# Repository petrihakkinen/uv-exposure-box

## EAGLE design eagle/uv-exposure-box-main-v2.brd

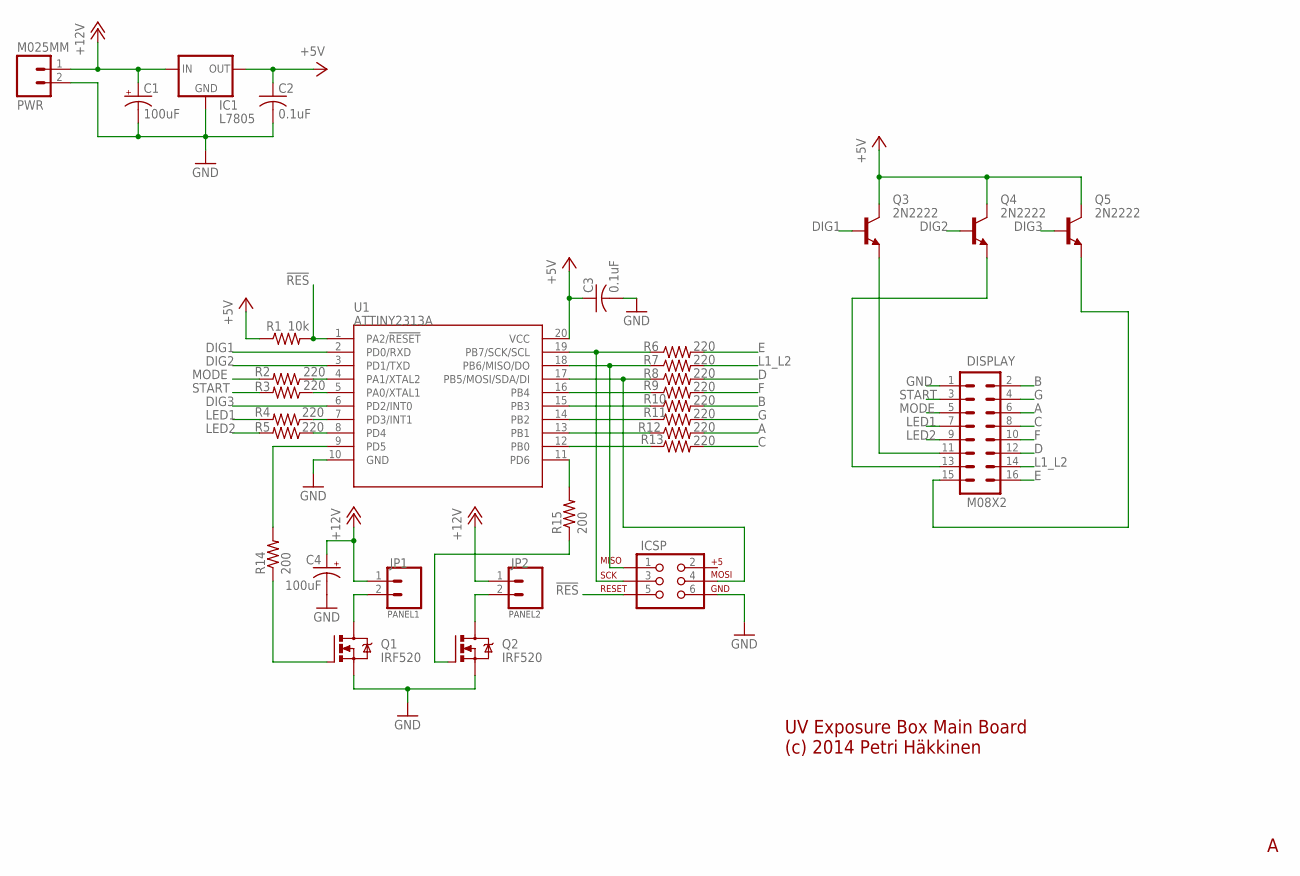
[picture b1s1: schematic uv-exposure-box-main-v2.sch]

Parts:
C1, C4: 100uF; E2,5-5
C2, C3: 0.1uF; C025-024X044
DISPLAY: M08X2; 2X8
IC1: L7805; TO220-IGO
ICSP: AVR_SPI_PRG_6PTH; 2X3
JP1, JP2: M025MM; SCREWTERMINAL-5MM-2
PWR: M025MM; SCREWTERMINAL-5MM-2
Q1, Q2: IRF520; TO220BV
Q3, Q4, Q5: 2N2222; TO92-EBC
R1: 10k; 0207/10
R2, R3, R4, R5, R6, R7, R8, R9, R10, R11, R12, R13: 220; 0207/10
R14, R15: 200; 0207/10
U1: ATTINY2313A; DIL20

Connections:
!RES: ICSP.5, R1.2, U1.1 (PA2/!RESET)
+5V: C2.1, C3.1, IC1.OUT, Q3.C, Q4.C, Q5.C, R1.1, U1.20 (VCC)
+12V: C1.+, C4.+, IC1.IN, JP1.1, JP2.1, PWR.1
A: DISPLAY.6, R12.2
B: DISPLAY.2, R10.2
C: DISPLAY.8, R13.2
D: DISPLAY.12, R8.2
DIG1: DISPLAY.11, Q3.B, Q3.E, U1.2 (PD0/RXD)
DIG2: Q4.B, U1.3 (PD1/TXD)
DIG3: Q5.B, U1.6 (PD2/INT0)
E: DISPLAY.16, R6.2
F: DISPLAY.10, R9.2
G: DISPLAY.4, R11.2
GND: C1.-, C2.2, C3.2, C4.-, DISPLAY.1, IC1.GND, ICSP.6, PWR.2, Q1.S, Q2.S, U1.10 (GND)
L1_L2: DISPLAY.14, R7.2
LED1: DISPLAY.7, R4.2
LED2: DISPLAY.9, R5.2
MODE: DISPLAY.5, R2.2
unnamed: R2.1, U1.4 (PA1/XTAL2)
unnamed: R3.1, U1.5 (PA0/XTAL1)
unnamed: DISPLAY.13, Q4.E
unnamed: DISPLAY.15, Q5.E
unnamed: Q1.G, R14.1
unnamed: R15.2, U1.11 (PD6)
unnamed: ICSP.3, R6.1, U1.19 (PB7/SCK/SCL)
unnamed: ICSP.1, R7.1, U1.18 (PB6/MISO/DO)
unnamed: ICSP.4, R8.1, U1.17 (PB5/MOSI/SDA/DI)
unnamed: R9.1, U1.16 (PB4)
unnamed: R10.1, U1.15 (PB3)
unnamed: R11.1, U1.14 (PB2)
unnamed: R12.1, U1.13 (PB1)
unnamed: R13.1, U1.12 (PB0)
unnamed: R4.1, U1.7 (PD3/INT1)
unnamed: R5.1, U1.8 (PD4)
unnamed: R14.2, U1.9 (PD5)
unnamed: JP1.2, Q1.D
unnamed: Q2.G, R15.1
unnamed: JP2.2, Q2.D
START: DISPLAY.3, R3.2

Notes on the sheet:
PANEL1
PANEL2
UV Exposure Box Main Board (c) 2014 Petri Häkkinen

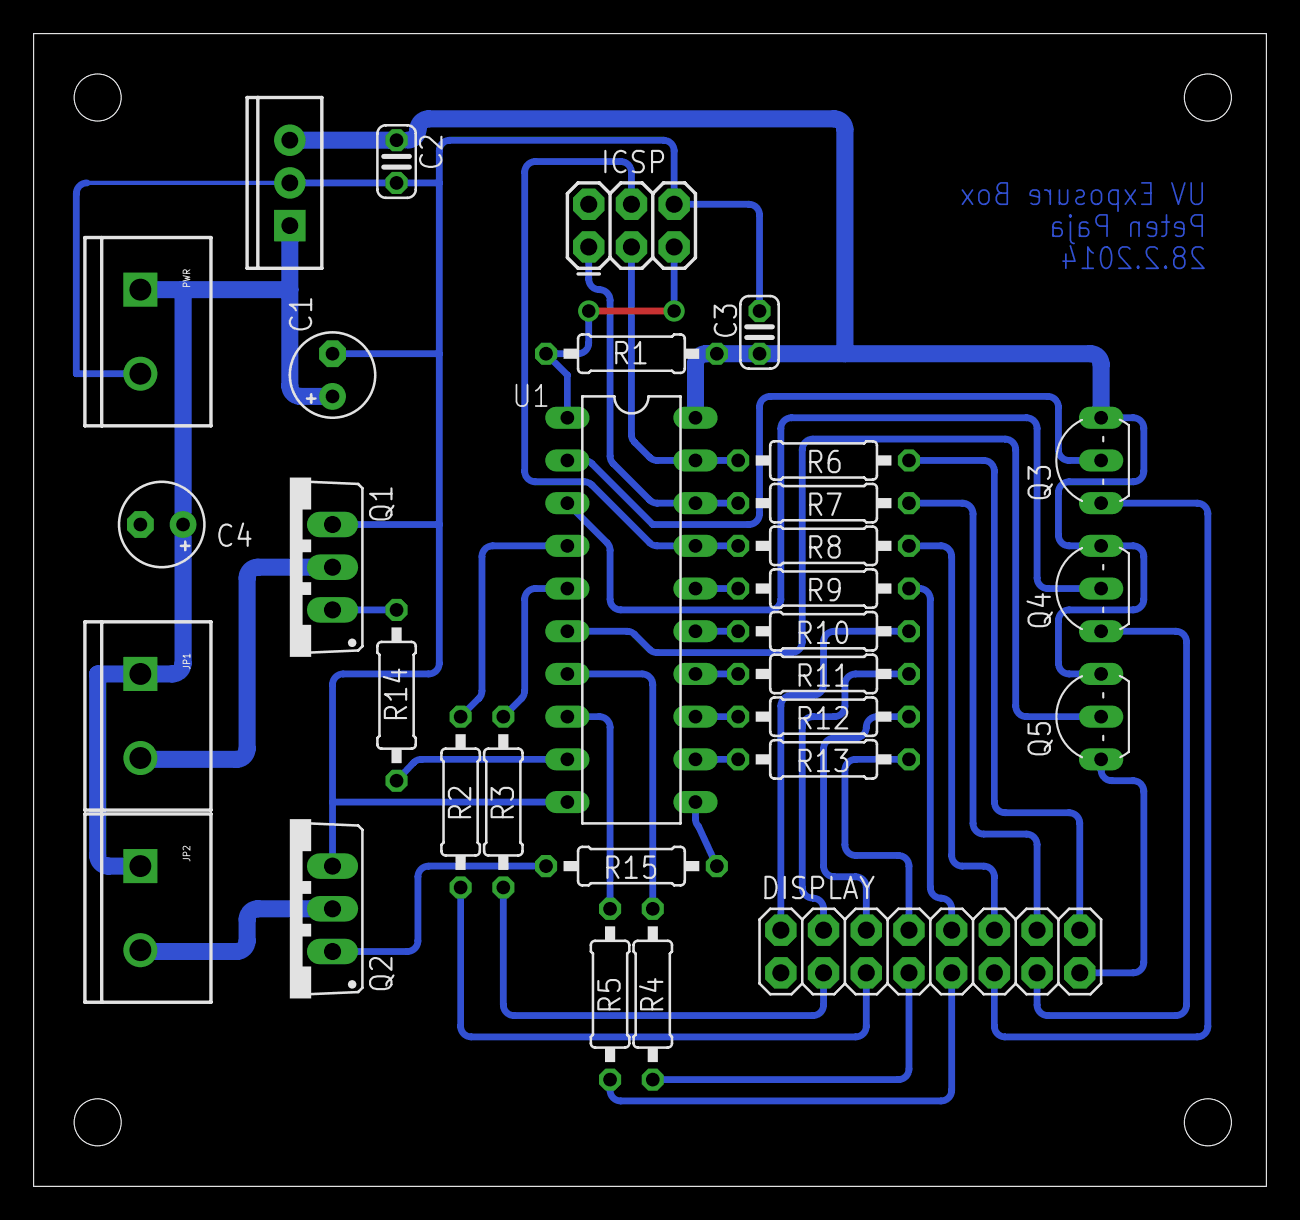
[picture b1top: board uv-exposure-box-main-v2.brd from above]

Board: 2 copper layers, 73.3 x 68.6 mm, 31 parts (0 on the bottom side), 39 nets.

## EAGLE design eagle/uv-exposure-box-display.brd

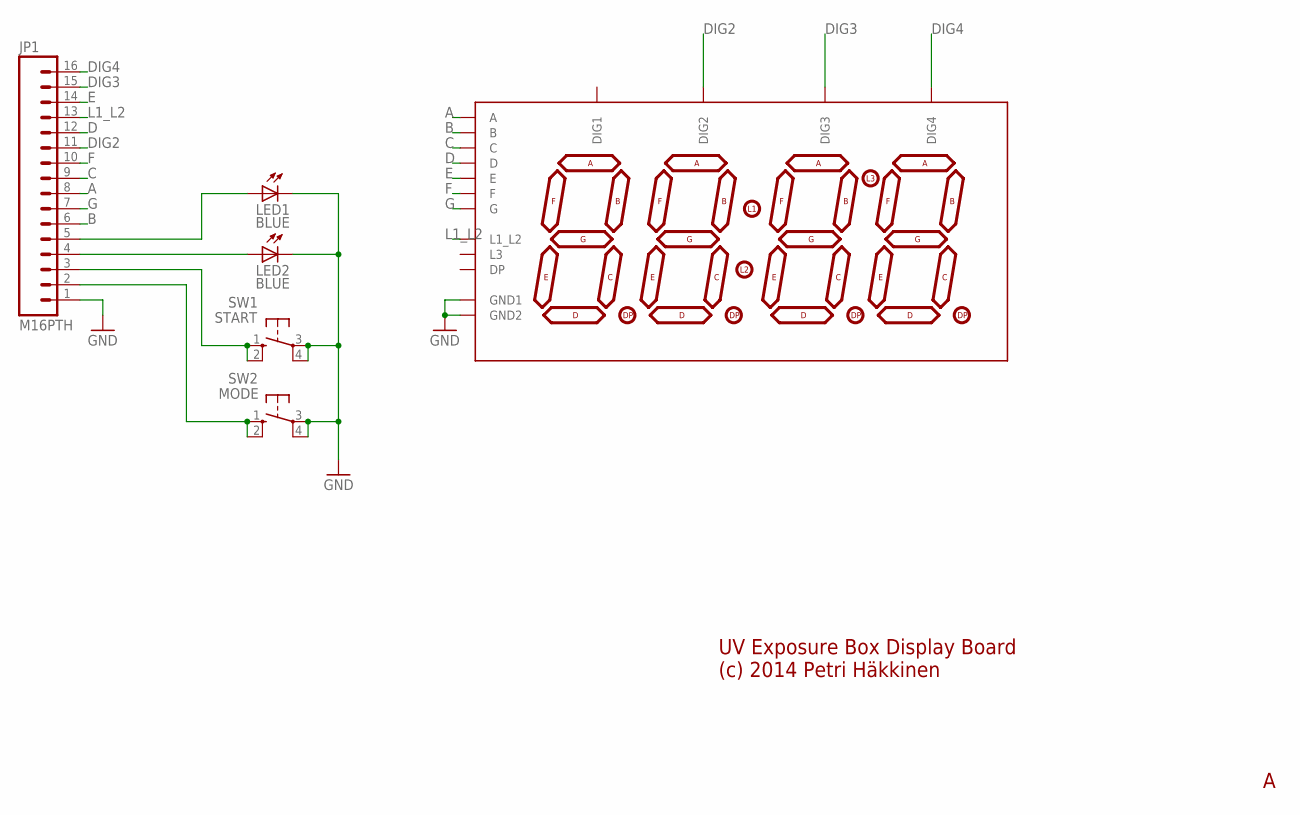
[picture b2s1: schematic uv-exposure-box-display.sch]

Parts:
JP1: M16PTH; 1X16
LED1, LED2: BLUE; LED3MM
SW1: START; B3F-10XX
SW2: MODE; B3F-10XX
U$1: 7-SEGMENT-4DIGIT; 7-SEGMENT-4DIGIT-YOUNGSUN

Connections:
A: JP1.8, U$1.14 (A)
B: JP1.6, U$1.16 (B)
C: JP1.9, U$1.13 (C)
D: JP1.12, U$1.3 (D)
DIG2: JP1.11, U$1.2 (DIG2)
DIG3: JP1.15, U$1.6 (DIG3)
DIG4: JP1.16, U$1.8 (DIG4)
E: JP1.14, U$1.5 (E)
F: JP1.10, U$1.11 (F)
G: JP1.7, U$1.15 (G)
GND: JP1.1, LED1.K (C), LED2.K (C), SW1.3, SW1.4 (P1), SW2.3, SW2.4 (P1), U$1.9 (GND1), U$1.12 (GND2)
L1_L2: JP1.13, U$1.4 (L1_L2)
unnamed: JP1.5, LED1.A
unnamed: JP1.4, LED2.A
unnamed: JP1.3, SW1.1 (S), SW1.2 (S1)
unnamed: JP1.2, SW2.1 (S), SW2.2 (S1)

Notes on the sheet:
UV Exposure Box Display Board (c) 2014 Petri Häkkinen

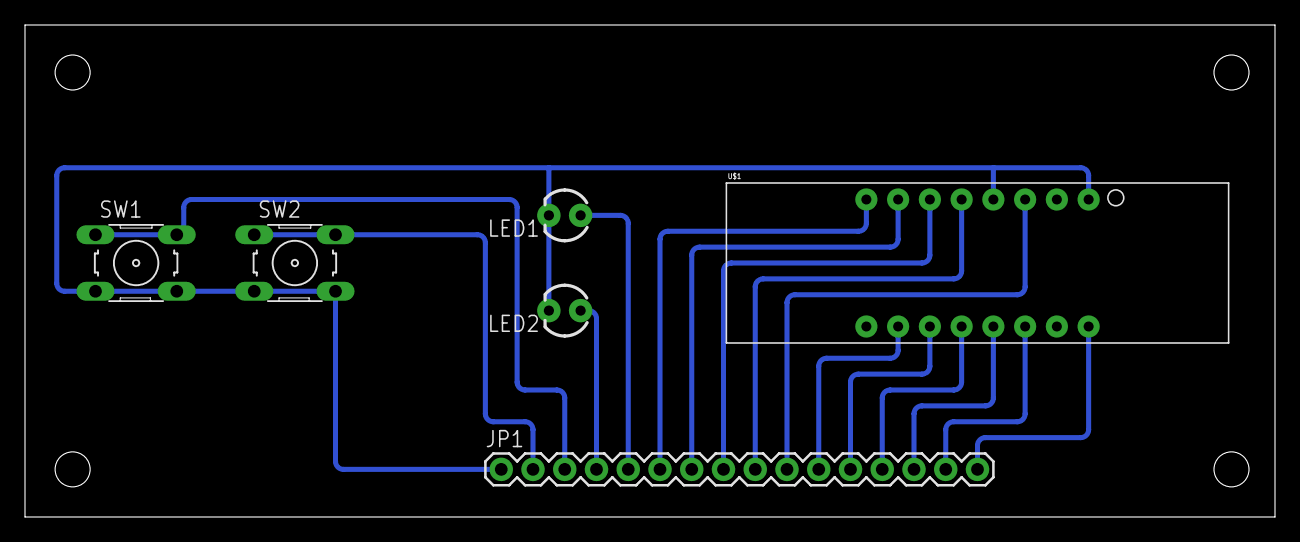
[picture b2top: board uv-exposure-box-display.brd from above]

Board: 2 copper layers, 100.0 x 39.4 mm, 6 parts (0 on the bottom side), 16 nets.

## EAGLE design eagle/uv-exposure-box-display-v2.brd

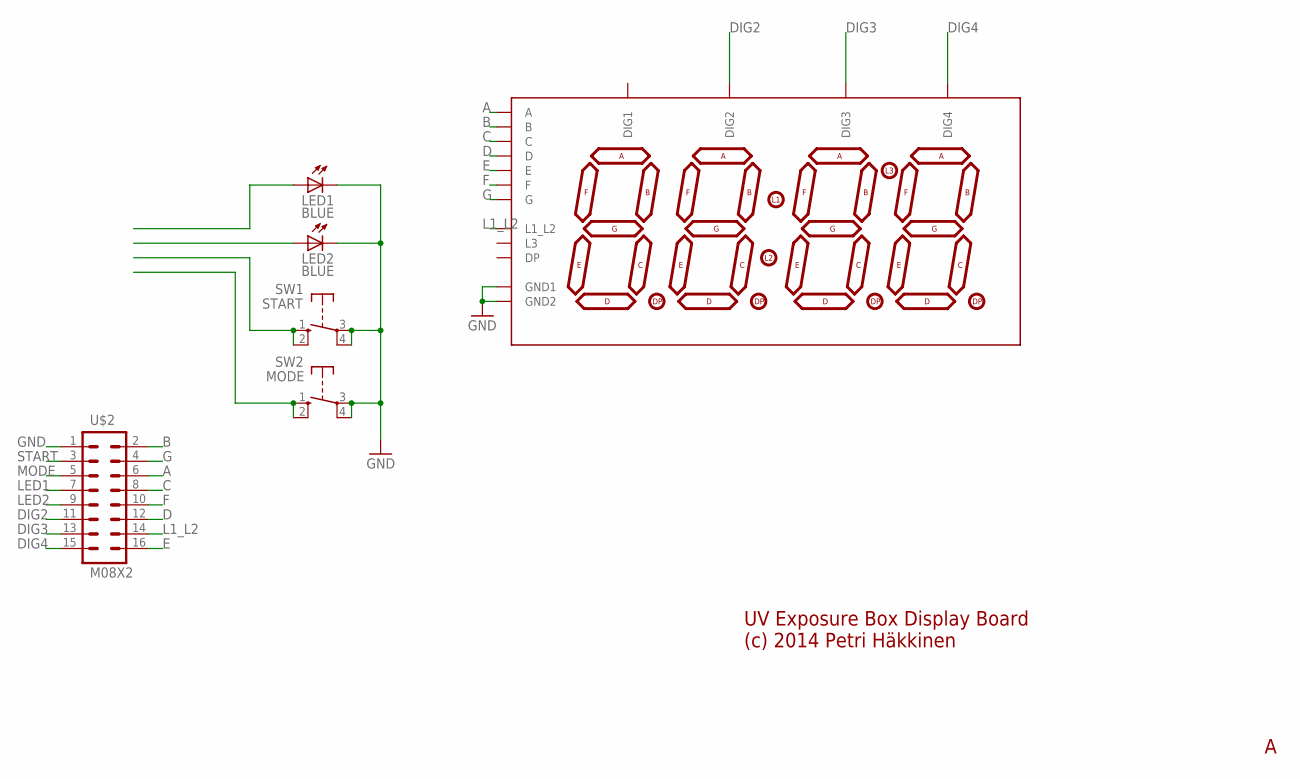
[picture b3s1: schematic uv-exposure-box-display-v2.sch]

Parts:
LED1, LED2: BLUE; LED3MM
SW1: START; DTE6K
SW2: MODE; DTE6K
U$1: 7-SEGMENT-4DIGIT; 7-SEGMENT-4DIGIT-YOUNGSUN
U$2: M08X2; 2X8

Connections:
A: U$1.14 (A), U$2.6
B: U$1.16 (B), U$2.2
C: U$1.13 (C), U$2.8
D: U$1.3 (D), U$2.12
DIG2: U$1.2 (DIG2), U$2.11
DIG3: U$1.6 (DIG3), U$2.13
DIG4: U$1.8 (DIG4), U$2.15
E: U$1.5 (E), U$2.16
F: U$1.11 (F), U$2.10
G: U$1.15 (G), U$2.4
GND: LED1.K (C), LED2.K (C), SW1.3, SW1.4, SW2.3, SW2.4, U$1.9 (GND1), U$1.12 (GND2), U$2.1
L1_L2: U$1.4 (L1_L2), U$2.14
LED1: LED1.A, U$2.7
LED2: LED2.A, U$2.9
MODE: SW2.1 (S), SW2.2 (S), U$2.5
START: SW1.1 (S), SW1.2 (S), U$2.3

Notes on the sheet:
UV Exposure Box Display Board (c) 2014 Petri Häkkinen

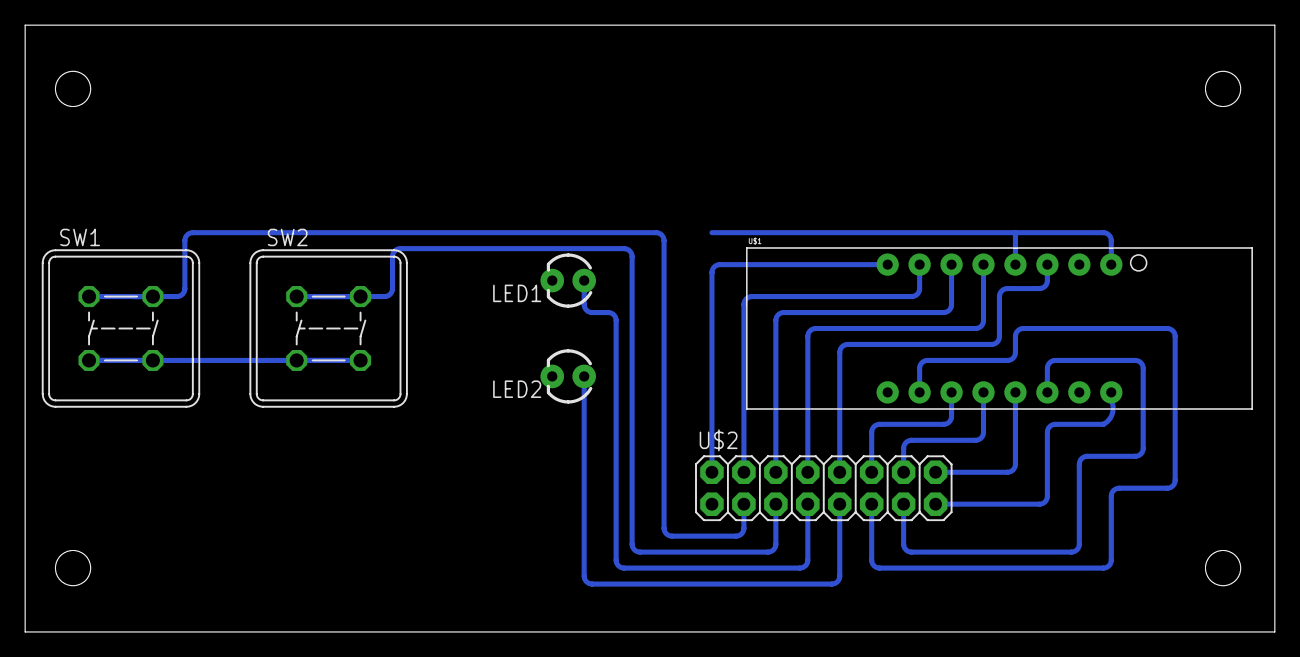
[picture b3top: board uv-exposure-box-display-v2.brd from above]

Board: 2 copper layers, 99.4 x 48.2 mm, 6 parts (0 on the bottom side), 16 nets.

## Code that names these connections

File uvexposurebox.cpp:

// UV Exposure Box Controller Board
//
// I/O Pins
//
// PA0		Start button (low active)
// PA1		Mode button (low active)
// PD0 		Digit 1 (digit is enabled when output is high)
// PD1		Digit 2
// PD2		Digit 3
// PD3		Up led
// PD4		Down led
// PD5		MOSFET up
// PD6		MOSFET down
// PB0		Seg C
// PB1		Seg A	(segment lit when output is low)
// PB2		Seg G
// PB3		Seg B
// PB4		Seg F
// PB5		Seg D
// PB6		L1_L2	(dots are lit when output is high)
// PB7		Seg E

#include <avr/io.h>
#include <avr/interrupt.h>
#include <avr/eeprom.h>
#include <util/delay.h>

#define BUTTON_START	1
#define BUTTON_MODE		2

#define SEG_A		2
#define SEG_B		8
#define SEG_C		1
#define SEG_D		32
#define SEG_E		128
#define SEG_F		16
#define SEG_G		4
#define SEG_DOTS	64

// millis implementation

volatile uint32_t _millis = 0;
volatile uint16_t _1000us = 0;

void initMillis()
{ 
	// set timer0 prescaler
	// overflow timer0 every 0.256 ms
	TCCR0B |= 1<<CS00;		// prescaler 1, use this for F_CPU 1Mhz
	//TCCR0B |= 1<<CS01;		// prescaler 1/8, use this for F_CPU 8Mhz

	// enable timer overflow interrupt
	TIMSK  |= 1<<TOIE0;

	// enable global interrupts
	sei();
}

// interrupts routine
// timer overflow occur every 0.256 ms
ISR(TIMER0_OVF_vect)
{
	_1000us += 256;
	while(_1000us > 1000)
	{
		_millis++;
		_1000us -= 1000;
	}
}

uint32_t millis()
{
	uint32_t m;
	cli();
	m = _millis;
	sei();
	return m;
}

uint8_t segdata[] = 
{
	(SEG_A|SEG_B|SEG_C|SEG_D|SEG_E|SEG_F)^191,		// 0
	(SEG_B|SEG_C)^191,								// 1
	(SEG_A|SEG_B|SEG_D|SEG_E|SEG_G)^191,			// 2
	(SEG_A|SEG_B|SEG_C|SEG_D|SEG_G)^191,			// 3
	(SEG_B|SEG_C|SEG_F|SEG_G)^191,					// 4
	(SEG_A|SEG_C|SEG_D|SEG_F|SEG_G)^191,			// 5
	(SEG_A|SEG_C|SEG_D|SEG_E|SEG_F|SEG_G)^191,		// 6
	(SEG_A|SEG_B|SEG_C)^191,						// 7
	(SEG_A|SEG_B|SEG_C|SEG_D|SEG_E|SEG_F|SEG_G)^191,// 8
	(SEG_A|SEG_B|SEG_C|SEG_D|SEG_F|SEG_G)^191,		// 9
};

uint8_t buttonState = 0;
uint8_t prevButtonState = 0;
uint8_t buttonPressed = 0;
uint8_t buttonReleased = 0;
uint8_t mode = 0;			// 0 = top, 1 = bottom, 2 = top+bottom
uint16_t exposureTime = 0;

void updateLeds()
{
	PORTD &= ~24;
	PORTD |= ((mode+1) & 3) << 3;
}

// Time in seconds. Dots are lit if dots == 0xff.
void updateDisplay(uint16_t time, uint8_t dots, uint8_t enableDigits = 0xff)
{
	static int digit = 0;
	digit++;
	if(digit == 3)
		digit = 0;

	// show minutes
	uint8_t mins = (time / 60) % 10;
	uint8_t secs = time % 60;
	uint8_t secs1 = secs / 10;
	uint8_t secs2 = secs % 10;

	if(digit == 0)
		time = mins;
	else if(digit == 1)
		time = secs1;
	else
		time = secs2;

	// turn off digits
	PORTD &= ~7;

	// set segments
	PORTB = segdata[time] | (dots & SEG_DOTS);

	// enable digit
	PORTD |= (1<<digit) & enableDigits;
}

void readConfig()
{
	exposureTime = eeprom_read_word(0);
	if(exposureTime >= 600)
		exposureTime = 30;	//DEBUG, was 120
}

void writeConfig()
{
	eeprom_write_word(0, exposureTime);
}

void updateButtons()
{
	// debouncing
	// read buttons only once every 5th ms
	static uint32_t lastButtonReadTime = 0;
	uint32_t ms = millis();
	if(millis() - lastButtonReadTime >= 5) {
		buttonState = (PINA & 3) ^ 3;
		lastButtonReadTime = ms;
	}

	buttonPressed = buttonState & (prevButtonState^255);
	buttonReleased = (buttonState^255) & prevButtonState;

	prevButtonState = buttonState;
}

void waitUntilButtonsReleased()
{
	do
	{
		updateButtons();
		updateDisplay(0, 0, 0);
	} while(buttonState != 0);
}

void timeSetup()
{
	uint8_t mins = exposureTime/60;
	uint8_t secs = exposureTime - mins*60;
	uint16_t blink = 512;

	// edit minutes
	while((buttonPressed & BUTTON_MODE) == 0)
	{
		updateButtons();
		exposureTime = mins * 60;
		updateDisplay(exposureTime, -1, blink < 512 ? 1 : 0);
		if(buttonPressed & BUTTON_START)
		{
			mins = (mins+1) % 10;
			blink = 0;
		}
		_delay_ms(1);
		blink = (blink+2) & 1023;
	}

	buttonPressed = 0;
	blink = 0;

	// edit seconds
	while((buttonPressed & BUTTON_MODE) == 0)
	{
		updateButtons();
		exposureTime = mins * 60 + secs;
		updateDisplay(exposureTime, -1, blink < 512 ? 7 : 1);
		if(buttonPressed & BUTTON_START)
		{
			secs = (secs+5) % 60;
			blink = 0;
		}
		_delay_ms(1);
		blink = (blink+2) & 1023;
	}

	writeConfig();
	waitUntilButtonsReleased();
}

void exposure()
{
	waitUntilButtonsReleased();

	uint32_t startTime = millis();
	uint16_t startButtonDownTime = 0;
	uint16_t blink = 0;

	// turn on mosfets
	PORTD |= (mode+1)<<5;

	while(true)
	{
		uint16_t elapsedTime = (millis() - startTime)/1000;
		uint16_t time = exposureTime - elapsedTime;
		if(elapsedTime >= exposureTime)
			time = 0;
		updateButtons();

		updateDisplay(time, blink < 512 ? -1 : 0, blink < 512 ? 0xff : 0);

		// exposure finished?
		if(time == 0)
		{
			blink = (blink + 2) & 1023;

			// turn off mosfets
			PORTD &= ~(32+64);

			if(buttonState & BUTTON_START)
				break;
		}

		// cancel exposure if start button is held down
		if(buttonState & BUTTON_START)
			startButtonDownTime++;
		else
			startButtonDownTime = 0;
		if(startButtonDownTime == 500)
			break;		

		_delay_ms(1);
	}

	// turn off mosfets
	PORTD &= ~(32+64);

	waitUntilButtonsReleased();
}

int main()
{
	// set button pins to input with pull ups enabled
	DDRA = 0;
	PORTA = 3;

	// set digit and segment pins to output
	DDRB = 255;
	DDRD = 127;

	readConfig();
	updateLeds();
	initMillis();

	uint16_t modeButtonDownTime = 0;
	uint16_t startButtonDownTime = 0;

	while(true)
	{
		updateButtons();
		updateDisplay(exposureTime, -1);

		// start exposure
		if(buttonState & BUTTON_START)
			startButtonDownTime++;
		else
			startButtonDownTime = 0;
		if(startButtonDownTime == 500)
			exposure();

		// toggle mode
		if(buttonReleased & BUTTON_MODE)
		{
			mode = (mode + 1) % 3;
			updateLeds();
		}

		// enter time setup mode?
		if(buttonState & BUTTON_MODE)
			modeButtonDownTime++;
		else
			modeButtonDownTime = 0;
		if(modeButtonDownTime == 1500)
			timeSetup();

		_delay_ms(1);
	}	

	return 0;
}

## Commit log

2016-05-17 Added files.

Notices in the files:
parts and their libraries:
SparkFun-LED: Licensing: CC v3.0 Share-Alike You are welcome to use this library for commercial purposes.
